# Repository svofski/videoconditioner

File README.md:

# Non-standard RGB video conditioner
RGB video input for Altera DE1 board + PAL Modulator
====================================================
This is an experimental video capture project. 
The goal is to capture poorly modulated RGB + Sync signal as produced by an old Soviet home PC,
detect sync, massage the signal levels, insert correct sync pulses, add PAL colour modulation
and output a signal that would be acceptable by a modern colour TV.

Вектор-06ц is the particular computer that I had in mind. Its video generation circuit is
infamous for blatant disregard of all existing video standards at once, which makes it
rather difficult to connect it to modern monitors and televisions.

Outline
-------
The main platform is Altera DE1 FPGA board. It is fairly outdated, but it's the one that I have
on my bench. Going up to more modern FPGA kits is easy.

A working PAL modulator that works well in my [vector06cc FPGA
replica](https://github.com/svofski/vector06cc) of the same computer already exists.

To sample RGB + Sync video signal one needs a decent speed ADC, preferrably with 4 channels,
or a special video capture chip. I found nothing that would suit the job easily available.
However, I found out about a neat trick of using LVDS input pairs available on FPGA chips
to implement custom sigma-delta ADC. No need for special chips!

The basic working principles of such ADC are described in the paper called
["Leveraging FPGA and CPLD digital logic to implement analog to digital converters"](http://www.embedded.com/design/configurable-systems/4008891/Leveraging-FPGA-and-CPLD-digital-logic-to-implement-analog-to-digital-converters) 
by Ted Marena. There's also an excellent explanation and demonstration of the principle in [One Bit ADC](http://www.youtube.com/watch?v=DTCtx9eNHXE)
video by Jeri Ellsworth.

Block diagram
-------------
Here's a simplified diagram of the project:

The video signal comprised of H+V composite sync and R, G, B signals is level-shifted to be within
range of LVDS inputs (see schematic) and is fed into the ADC. The ADC modules feed back the resulting
PDM signal to the negative side of LVDS inputs, and to the input averaging filter. The recovered
PCM signal is formed on the output of the filter. There are variations of input filters in the source code.

The recovered sync signal is passed to the input of sync detector module, which tries its best to 
recover horizontal and vertical sync pulses. It's designed to be able to cope with bizarre sync signals
produced by bizarre computers. It does the job with variable success. Usually the problems are of electrical
rather than of logical nature. For example, Вектор-06ц is known to have no equalization pulses, which
results in huge amplitude jumps during vertical sync or even simply empty lines.

The resulting sync, R, G, B signals are fed into the video generator module. It consists of sync generator
and PAL modulator. The outputs are chroma, luma and mixed CVBS composite signals. They are output either
using primitive linear DAC on VGA connector of DE1 board, or using a sigma-delta modulator. The latter
allows for having separate luma + chroma (S-Video) signals on the output. 

Generating output
-----------------
S-video using a sigma-delta DAC is very simple:
```
reg [DAC_RESOLUTION:0] ydac;
reg [DAC_RESOLUTION:0] cdac;
always @(posedge clk_out)
begin
    ydac <= ydac[DAC_RESOLUTION-1:0] + tv_luma[RESOLUTION-1:RESOLUTION-DAC_RESOLUTION]; 
    cdac <= cdac[DAC_RESOLUTION-1:0] + tv_chroma[RESOLUTION-1:RESOLUTION-DAC_RESOLUTION]; 
end

assign GPIO_0[10] = ydac[DAC_RESOLUTION];
assign GPIO_0[11] = cdac[DAC_RESOLUTION];
```

Linear DAC on VGA pins of DE1 board is more interesting. The resistor DAC on DE1 allows 4 bits per channel,
or just 16 levels. This is not a lot for composite analog video. Here's what a saw waveform looks like
if only 4 bits are used:

However with a little bit of magic, [described in detail in my article here](http://sensi.org/~svo/de1videodac/),
it is possible to get much higher resolution from this DAC. Here's an example:

The magic DAC is implemented using a look-up table:
```
dactable dactaklakpak(.address(tv_cvbs), .clock(clkpalFSC), .q(dacval));
assign VGA_R = dacval[3:0];
assign VGA_G = dacval[7:4];
assign VGA_B = dacval[11:8];
```

Project files
=============
 * [hw](https://github.com/svofski/videoconditioner/tree/vector06c/hw) contains KiCad files for the DE1 addon board. Check out the [schematic](https://github.com/svofski/videoconditioner/tree/vector06c/hw/videoadc.pdf).
 * [iverilog](https://github.com/svofski/videoconditioner/tree/vector06c/iverilog) contains simulation of video signals as produced by BK-0010, and their detection
 * [src](https://github.com/svofski/videoconditioner/tree/vector06c/src) Altera Quartus II project and synthesizable core

Results
=======
The input board looks like this:

Single channel, B&W+Sync only with BK-0010:

Single channel passthrough from C64. Signal sampled and output on DE1 VGA pins without any conditioning. Image credit: Deus ex Machina by Crest/Oxyron.

RGB+Sync from Vector-06c, internally PAL modulated in FPGA (captured by TV tuner)

[Work log on a forum (in Russian)](http://zx-pk.ru/showthread.php?t=23833)

Conclusion
==========
This is a research project and I never made it into a finished box with just power plug
and connectors. It works, but is not perfect. The results on my monitor are acceptable.
There were some problems with PAL encoding that I could not resolve that I observed on a couple of older TV sets. 
They are not related to the main focus of the project however: sampling video signals using nothing but a few LVDS pins.

It is definitely possible to capture low-spec video signals with a 10 year old FPGA using
only a few additional discrete components. The practical aspects of this
depend on the situation. Where reliability matter and source signal is known to be
within the specifications, a dedicated chip
like TVP7002 would most likely do better. One interesting example of a project that uses TVP7002
is [Grabor](http://www.rpg.fi/desaster/blog/2013/04/19/vga-framegrabbing-with-tvp7002/).
But with a such chip I would not be able to extract nonstandard 
video signal from Вектор-06ц, just like my monitor cannot do that. Where flexibility and fine control is
required, being able to implement video decoding on the lowest possible level can be beneficial.

The quality of input suffers from quite a bit of noise. I believe part of this is due to really
long electrical connections that are hard to shorten because of the way the connectors on the board are done.
In case of practical application it should be possible to improve the noise characteristics by
implementing the inputs using shorter, carefully layed out trace pairs, hopefully reducing parasitic
capacitance of the connections, thus allowing higher sampling frequency. Finding an optimal configuration
of PCB layout for such application would be an interesting project in itself.

References
==========
 - [Leveraging FPGA and CPLD Digital Logic to Implement Analog To Digital Converters](https://github.com/svofski/videoconditioner/tree/vector06c/whitepapers/CreatingAnADCUsingFPGAResources.PDF) LatticeSemi Whitepaper
 - [Simple Sigma-Delta ADC](https://github.com/svofski/videoconditioner/tree/vector06c/whitepapers/SimpleSigmaDeltaADCDocumentation.PDF) LatticeSemi RD1066
 - [FPGA RGB2VGA](https://sites.google.com/site/tandycocoloco/rgb2vga) scan doubler project by Felipe Antoniosi uses LVDS inputs to implement a successive approximation ADC

-------

2014-2015 Viacheslav Slavinsky, https://www.sensi.org/~svo

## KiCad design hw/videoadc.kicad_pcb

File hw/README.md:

These are KiCAD design files for Video ADC addon for DE1 FPGA Board.

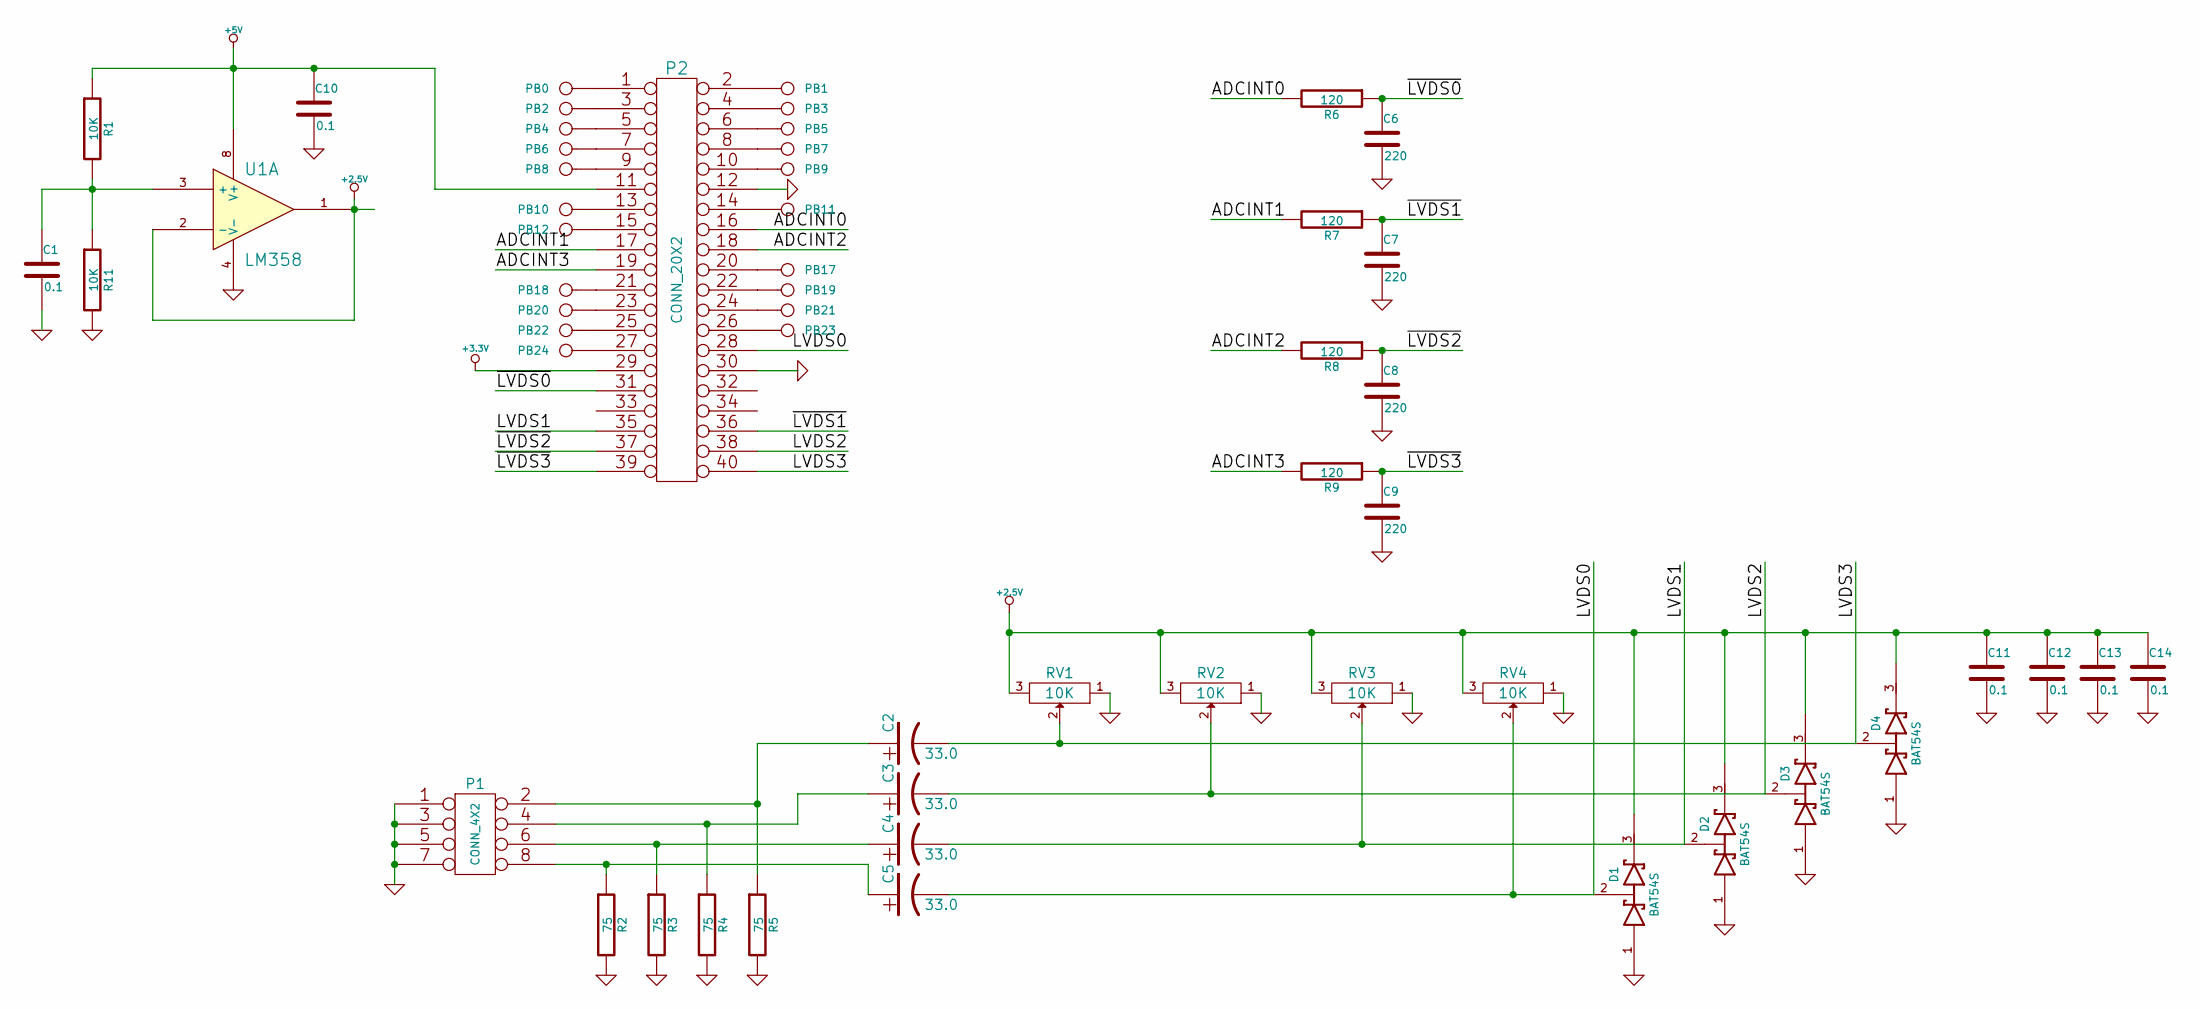
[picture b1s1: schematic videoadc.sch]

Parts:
C1, C10, C11, C12, C13, C14: 0.1
C2, C3, C4, C5: 33.0
C6, C7, C8, C9: 220
D1, D2, D3, D4: BAT54S
P1: CONN_4X2
P2: CONN_20X2
PB0, PB1, PB2, PB3, PB4, PB5, PB6, PB7, PB8, PB9, PB10, PB11, PB12, PB17, PB18, PB19, PB20, PB21, PB22, PB23, PB24: CONN_1
R1, R11: 10K
R2, R3, R4, R5: 75
R6, R7, R8, R9: 120
RV1, RV2, RV3, RV4: 10K
U1: LM358

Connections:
+2.5V: C11.1, C12.1, C13.1, C14.1, D1.3 (cathode), D2.3 (cathode), D3.3 (cathode), D4.3 (cathode), RV1.3, RV2.3, RV3.3, RV4.3, U1.1, U1.2 (-)
+3.3V: P2.29
+5V: C10.1, P2.11, R1.1, U1.8 (V+)
/ADCINT0: P2.16, R6.2
/ADCINT1: P2.17, R7.2
/ADCINT2: P2.18, R8.2
/ADCINT3: P2.19, R9.2
/LVDS0: C5.2, D1.2 (AK), P2.28, RV4.2
/LVDS1: C4.2, D2.2 (AK), P2.35, RV3.2
/LVDS2: C3.2, D3.2 (AK), P2.38, RV2.2
/LVDS3: C2.2, D4.2 (AK), P2.40, RV1.2
/~LVDS0: C6.1, P2.31, R6.1
/~LVDS1: C7.1, P2.36, R7.1
/~LVDS2: C8.1, P2.37, R8.1
/~LVDS3: C9.1, P2.39, R9.1
GND: C1.2, C6.2, C7.2, C8.2, C9.2, C10.2, C11.2, C12.2, C13.2, C14.2, D1.1 (Anode), D2.1 (Anode), D3.1 (Anode), D4.1 (Anode), P1.1, P1.3, P1.5, P1.7, P2.12, P2.30, R2.2, R3.2, R4.2, R5.2, R11.2, RV1.1, RV2.1, RV3.1, RV4.1, U1.4 (V-)
unnamed: C1.1, R1.2, R11.1, U1.3 (+)
unnamed: C2.1, P1.2, R5.1
unnamed: C3.1, P1.4, R4.1
unnamed: C4.1, P1.6, R3.1
unnamed: C5.1, P1.8, R2.1
unnamed: P2.1, PB0.1
unnamed: P2.2, PB1.1
unnamed: P2.3, PB2.1
unnamed: P2.4, PB3.1
unnamed: P2.5, PB4.1
unnamed: P2.6, PB5.1
unnamed: P2.7, PB6.1
unnamed: P2.8, PB7.1
unnamed: P2.9, PB8.1
unnamed: P2.10, PB9.1
unnamed: P2.13, PB10.1
unnamed: P2.14, PB11.1
unnamed: P2.15, PB12.1
unnamed: P2.20, PB17.1
unnamed: P2.21, PB18.1
unnamed: P2.22, PB19.1
unnamed: P2.23, PB20.1
unnamed: P2.24, PB21.1
unnamed: P2.25, PB22.1
unnamed: P2.26, PB23.1
unnamed: P2.27, PB24.1

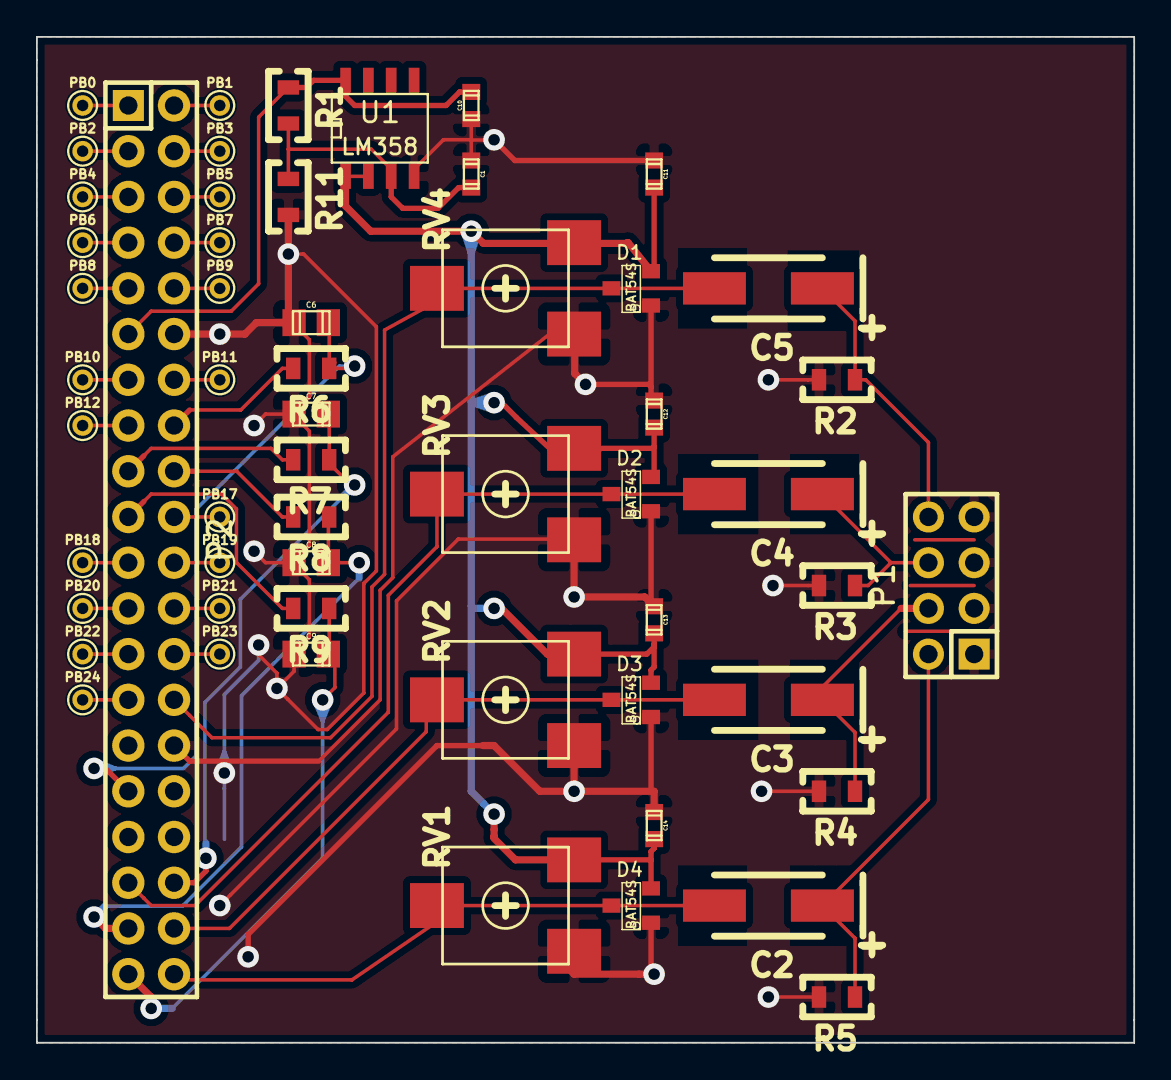
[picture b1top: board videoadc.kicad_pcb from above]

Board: 2 copper layers, 61.0 x 55.9 mm, 56 parts (0 on the bottom side), 41 nets.

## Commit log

2014-08-03 adaptive threshold so that DC drift on BK-0010 is not a terminal issue anymore (test: PAINT(11,11) -> white screen -> used to be disaster)
2014-08-03 i don't get it...
2014-08-03 kkk
    ,,,
2014-08-05 advances
    this is for 470 ohm / 220 pF filter, which seems to be ringing less and
    therefore filter better
    - the filter is now fc=0.025 (0.1)
    - adaptive threshold/black level
    - 6-bit linear DAC on VGA connector + some test signals
2014-08-05 coeffs
2014-08-08 6-bit dec with ROM table vector-06c like sync: shortening hsync pulses very long (23 lines long) sync pulse
2014-08-08 gitignore
2014-08-09 attempt to make a locked loop for hsync (untested)
    keep 64us loop como sea, but correct it on negative pulses — should
    work great with vector-06c kind of sync
    it should be easy to add horizontal offset now, just pass hsync through
    a delay
2014-08-10 decent sync verified on real vector-06c
    - horizontal delay added (32)
    - vsync shortened by half
    result: frame well centered
    back porch added so blue/gray stands out above black now, but it's not
    delayed with hsync so perhaps not ideal
2014-08-10 delayed porch with hsync
2014-08-10 better matched vsync simulation
2014-08-12 full color ADC works
    levels still need some tuning, especially blue appears to be more like
    on/off
2014-08-12 full colour gamut of vector-06c can be seen
    - added floorlevel to syncdetect, though it's not of much use
    - SW[5] turns on pal line alternation (useful for my receivers)
    - adjusted output levels in video modulator, I think the output is
    better balanced now
2014-08-13 tweaks tweaks tweaks
    also updated the schematic with actual values
2014-08-14 restored color intensity to lower value
    …because the monitor doesn't like too much of it
2015-09-03 schematic fluff
2015-09-04 added referenced whitepapers
2015-09-04 Makefile for simulation
2015-09-04 gtkwave screenshot
2015-09-04 schematic in png
2015-09-04 bw schematic
2015-09-04 Create gh-pages branch via GitHub
2015-09-05 diagram svg
2015-09-05 renamed to diagram.svg
2015-09-05 diagram.png
2015-09-05 dac waveforms
2015-09-06 fuck ruby, fuck jekyll, fuck everythingwq
2015-09-06 remove index.html
2015-09-06 styles
2015-09-06 section
2015-09-06 config.yml
2015-09-06 flatdoc
